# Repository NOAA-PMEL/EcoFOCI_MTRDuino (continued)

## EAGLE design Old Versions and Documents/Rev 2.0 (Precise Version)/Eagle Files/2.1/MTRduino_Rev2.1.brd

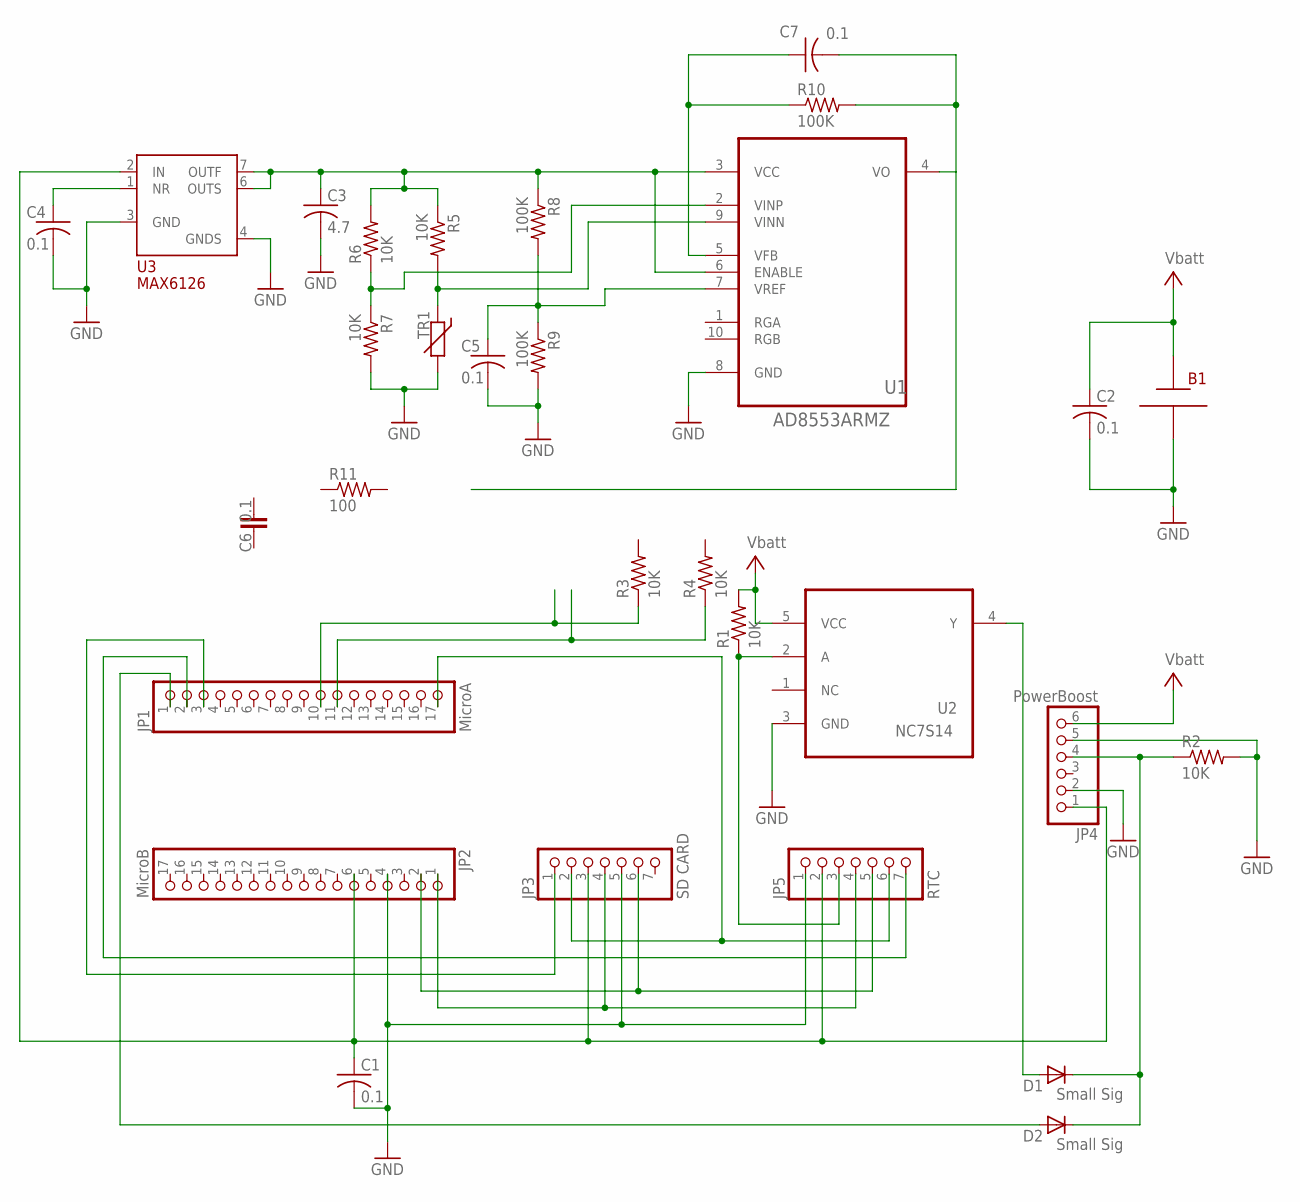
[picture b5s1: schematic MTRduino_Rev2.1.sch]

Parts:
B1: 2x AA BATT; BATT_AA2
C1, C2, C4, C5, C6, C7: 0.1; C0603
C3: 4.7; C0603
D1, D2: Small Sig; SOD-323F
JP1: MicroA; 1X17
JP2: MicroB; 1X17
JP3: SD CARD; 1X07
JP4: PowerBoost; 1X06
JP5: RTC; 1X07
R1, R2, R3, R4, R5, R6, R7: 10K; R0603
R8, R9, R10: 100K; R0603
R11: 100; R0603
TR1: 10K; R-5
U1: AD8553ARMZ; SOP50P490X110-10N
U2: NC7S14; SOT95P280X145-5N
U3: MAX6126; SOIC127P600X175-8N

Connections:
GND: B1.-, C1.2, C2.2, C3.2, C4.2, C5.2, JP2.4, JP3.5, JP4.2, JP4.5, JP5.1, R2.2, R7.2, R9.2, TR1.2, U1.8 (GND), U2.3 (GND), U3.3 (GND), U3.4 (GNDS)
unnamed: D1.A, U2.4 (Y)
unnamed: C7.2, R10.2, U1.4 (VO)
unnamed: JP1.2, JP5.7
unnamed: C4.1, U3.1 (NR)
unnamed: R6.1, R7.1, U1.2 (VINP)
unnamed: R5.2, TR1.1, U1.9 (VINN)
unnamed: C7.1, R10.1, U1.5 (VFB)
unnamed: JP1.10, R3.1
unnamed: JP1.11, R4.1
unnamed: C5.1, R8.2, R9.1, U1.7 (VREF)
unnamed: C3.1, R5.1, R6.2, R8.1, U1.3 (VCC), U1.6 (ENABLE), U3.6 (OUTS), U3.7 (OUTF)
unnamed: JP5.3, R1.1, U2.2 (A)
unnamed: JP1.17, JP3.2, JP5.6
unnamed: D2.A, JP1.1
unnamed: D1.C, D2.C, JP4.4, R2.1
unnamed: JP2.1, JP3.4, JP5.4
unnamed: JP2.2, JP3.6, JP5.5
unnamed: C1.1, JP2.6, JP3.3, JP4.1, JP5.2, U3.2 (IN)
unnamed: JP1.3, JP3.1
V+: B1.+, C2.1, JP4.6, R1.2, U2.5 (VCC)

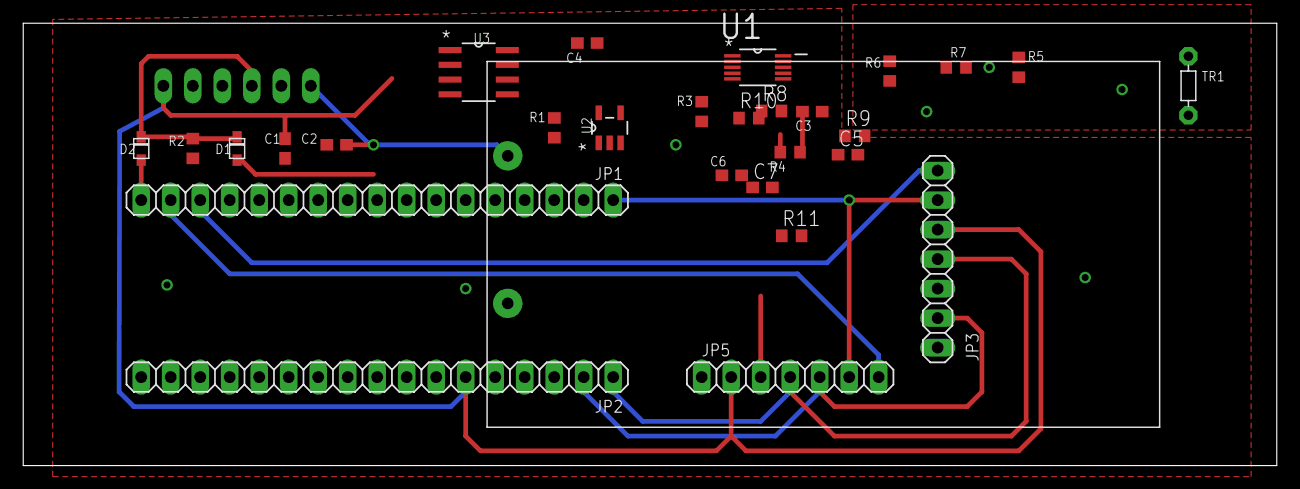
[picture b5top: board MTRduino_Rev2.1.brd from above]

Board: 2 copper layers, 107.9 x 38.1 mm, 30 parts (1 on the bottom side), 21 nets.

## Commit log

2018-01-04 1-4-18 Update
    Added Gerber Files, Schematic & Board PDFs, Mechanical Drawings, Temperature Calibration Example Worksheet; Updated Manuals
2018-11-15 cleanup
2018-11-15 more cleanup
